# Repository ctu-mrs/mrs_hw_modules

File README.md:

# MRS Modules
Modules for MRS drone distribution boards to add a specific funtionality the distribution boards do not provide.

These modules are equipped with 1x10 header with 2mm pitch providing the module with UART connection, 5V from USB and VBAT from battery.

## MRS Module Host

This PCB serves as a host for MRS Modules for development. It's functionality is simple: provide power for VBAT pins (can be supplied using the 5.5/2.5mm barrel connector), power for the module's MCU and serial communication between the user's computer and the module's MCU (usinng the USB2.0B mini connector).

The VBAT input of the module is designed to be either 4S or 6S LiPo battery, but can be anything the designed module is capable of. Check the module's VBAT capabilities before plugging in any power source in case it is unsuitable and could damage the module.

## MRS Module Templates
Three templates are provided in case you aim to implement your own module: Small, Medium and Large.

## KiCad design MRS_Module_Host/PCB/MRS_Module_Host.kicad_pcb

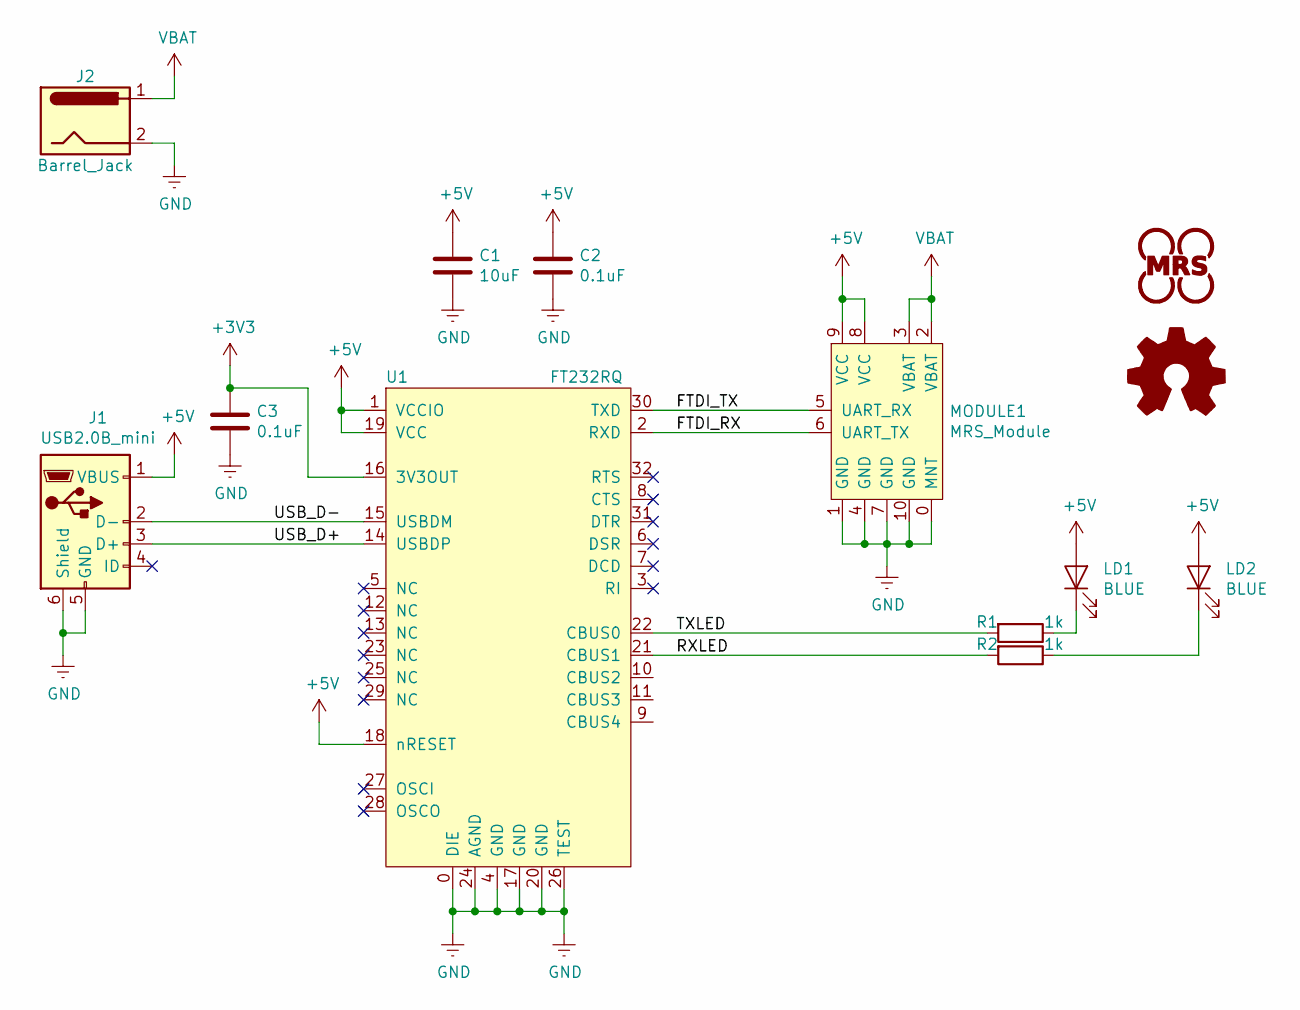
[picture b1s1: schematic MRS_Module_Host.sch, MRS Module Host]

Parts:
C1: 10uF; C0603; Farnell 2456110
C2, C3: 0.1uF; C0603; Farnell 2821272
J1: USB2.0B_mini; USB_Mini-B_Lumberg_2486_01_Horizontal
J2: Barrel_Jack; ADC-028-2-TR; Digikey 2073-DCJ200-05-A-K1-ACT-ND
LD1, LD2: D_LED_0603_BLUE; LED_0603; Farnell *
LOGO1: MRS_Logo; MRS_10mm
LOGO2: Logo_Open_Hardware_Small; OSHW-Logo_11.4x12mm_SilkScreen
MODULE1: MRS_Module; MRS_MODULE_MEDIUM
R1, R2: 1k; R0603; Farnell 2861864
U1: FT232RQ; QFN_32-5x5mm; Farnell 1146033

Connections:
+3V3: C3.1, U1.16 (3V3OUT)
+5V: C1.1, C2.1, J1.1 (VBUS), LD1.2 (A), LD2.2 (A), MODULE1.8 (VCC), MODULE1.9 (VCC), U1.1 (VCCIO), U1.18 (nRESET), U1.19 (VCC)
/FTDI_RX: MODULE1.6 (UART_TX), U1.2 (RXD)
/FTDI_TX: MODULE1.5 (UART_RX), U1.30 (TXD)
/RXLED: R2.2, U1.21 (CBUS1)
/TXLED: R1.2, U1.22 (CBUS0)
/USB_D+: J1.3 (D+), U1.14 (USBDP)
/USB_D-: J1.2 (D-), U1.15 (USBDM)
GND: C1.2, C2.2, C3.2, J1.5 (GND), J1.6 (Shield), J2.2, MODULE1.0 (MNT), MODULE1.1 (GND), MODULE1.4 (GND), MODULE1.7 (GND), MODULE1.10 (GND), U1.0 (DIE), U1.4 (GND), U1.17 (GND), U1.20 (GND), U1.24 (AGND), U1.26 (TEST)
unnamed: LD1.1 (K), R1.1
unnamed: LD2.1 (K), R2.1
VBAT: J2.1, MODULE1.2 (VBAT), MODULE1.3 (VBAT)

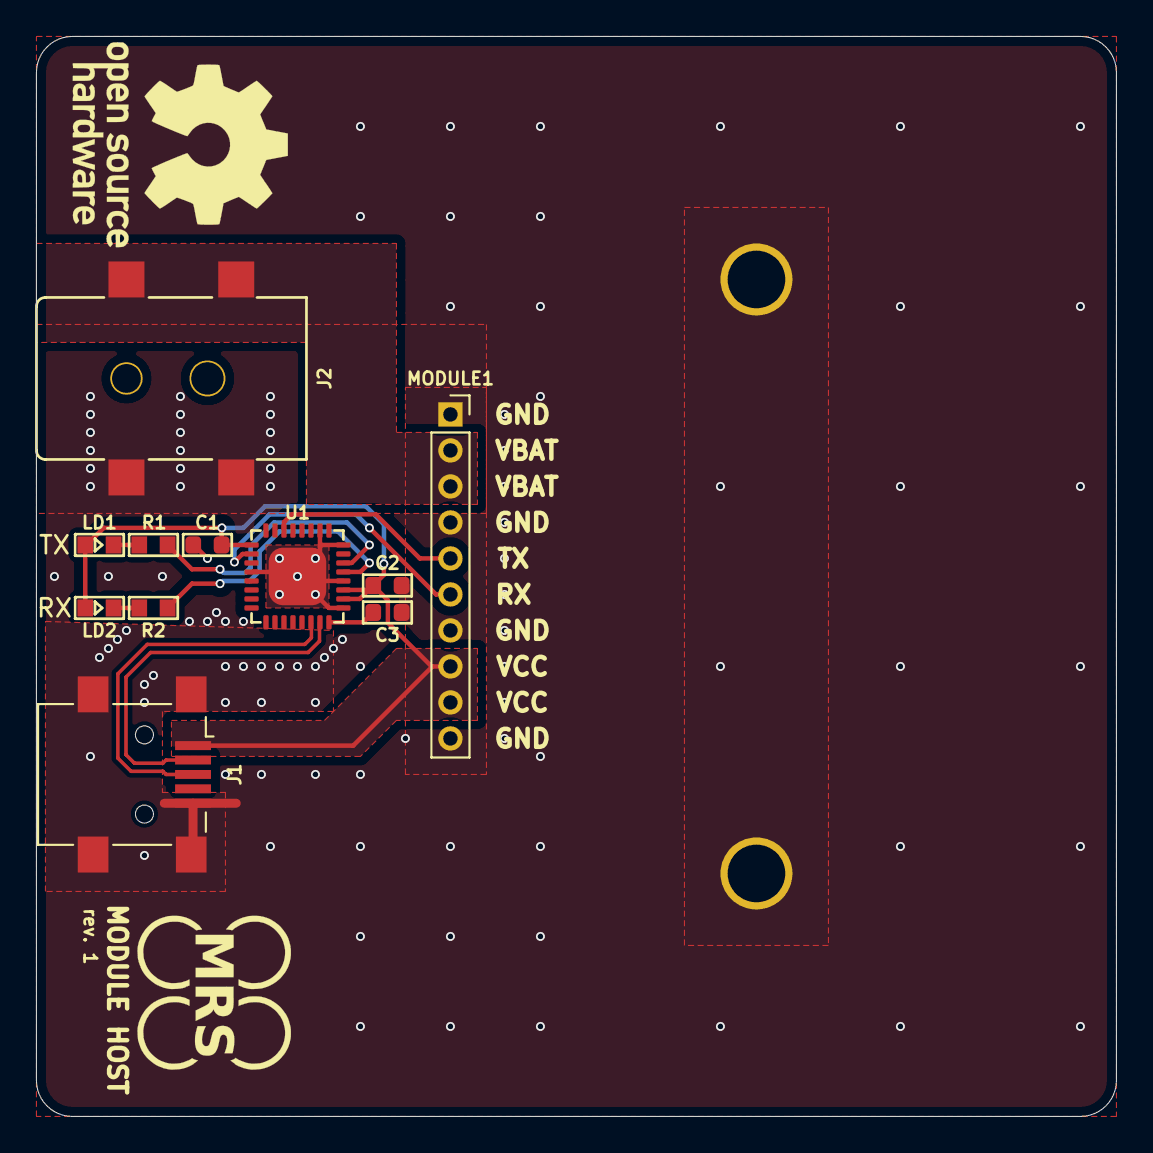
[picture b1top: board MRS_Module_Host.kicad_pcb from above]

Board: 2 copper layers, 60.0 x 60.0 mm, 13 parts (0 on the bottom side), 12 nets.

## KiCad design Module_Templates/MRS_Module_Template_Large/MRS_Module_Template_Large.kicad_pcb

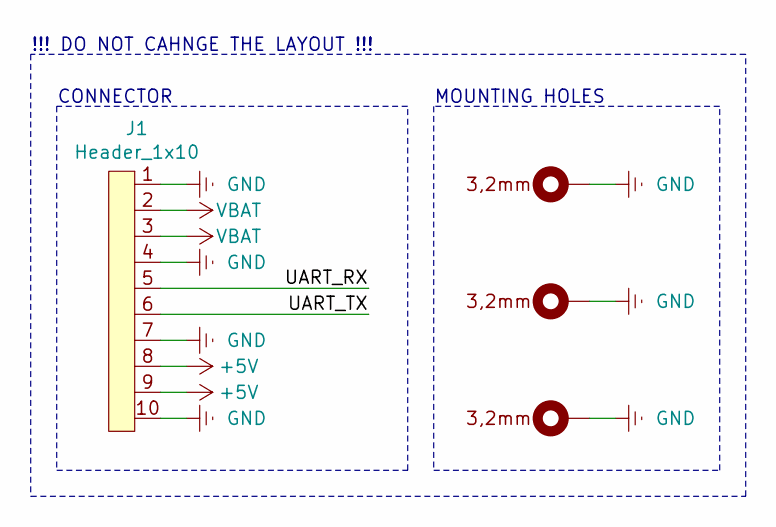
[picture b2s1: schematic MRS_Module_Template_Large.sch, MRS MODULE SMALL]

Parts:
H1, H2, H3: Mounting_hole_plated_3,2mm; Mounting_hole_plated_3,2mm_thin
J1: Header_1x10; PinHeader_1x10_P2.00mm_Vertical

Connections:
+5V: J1.8, J1.9
/UART_RX: J1.5
/UART_TX: J1.6
GND: H1.1, H2.1, H3.1, J1.1, J1.4, J1.7, J1.10
VBAT: J1.2, J1.3

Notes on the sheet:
CONNECTOR
MOUNTING HOLES
!!! DO NOT CAHNGE THE LAYOUT !!!

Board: 2 copper layers, 4 parts (1 on the bottom side), 3 nets, no tracks yet.

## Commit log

2021-02-09 added submodule
2021-02-09 Added UVDAR Module PCB and Firmware.
2021-02-09 Edit README to UVDAR Submodule.
2021-02-10 Changed uv_led_counter from uint16_t to uint32_t.
2021-02-10 Added documentation.
2021-02-10 Updated submodule.
2021-02-10 Added UVDAR Standalone.
2021-02-23 Added a basic template for custom modules.
2021-02-23 updated uvdar submodule.
2021-02-23 Added MRS Host module.
2021-02-23 Updated README.
